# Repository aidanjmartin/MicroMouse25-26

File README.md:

# MicroMouse25-26
This is the repo for SME Robotics Club MicroMouse for 2025-2026 year

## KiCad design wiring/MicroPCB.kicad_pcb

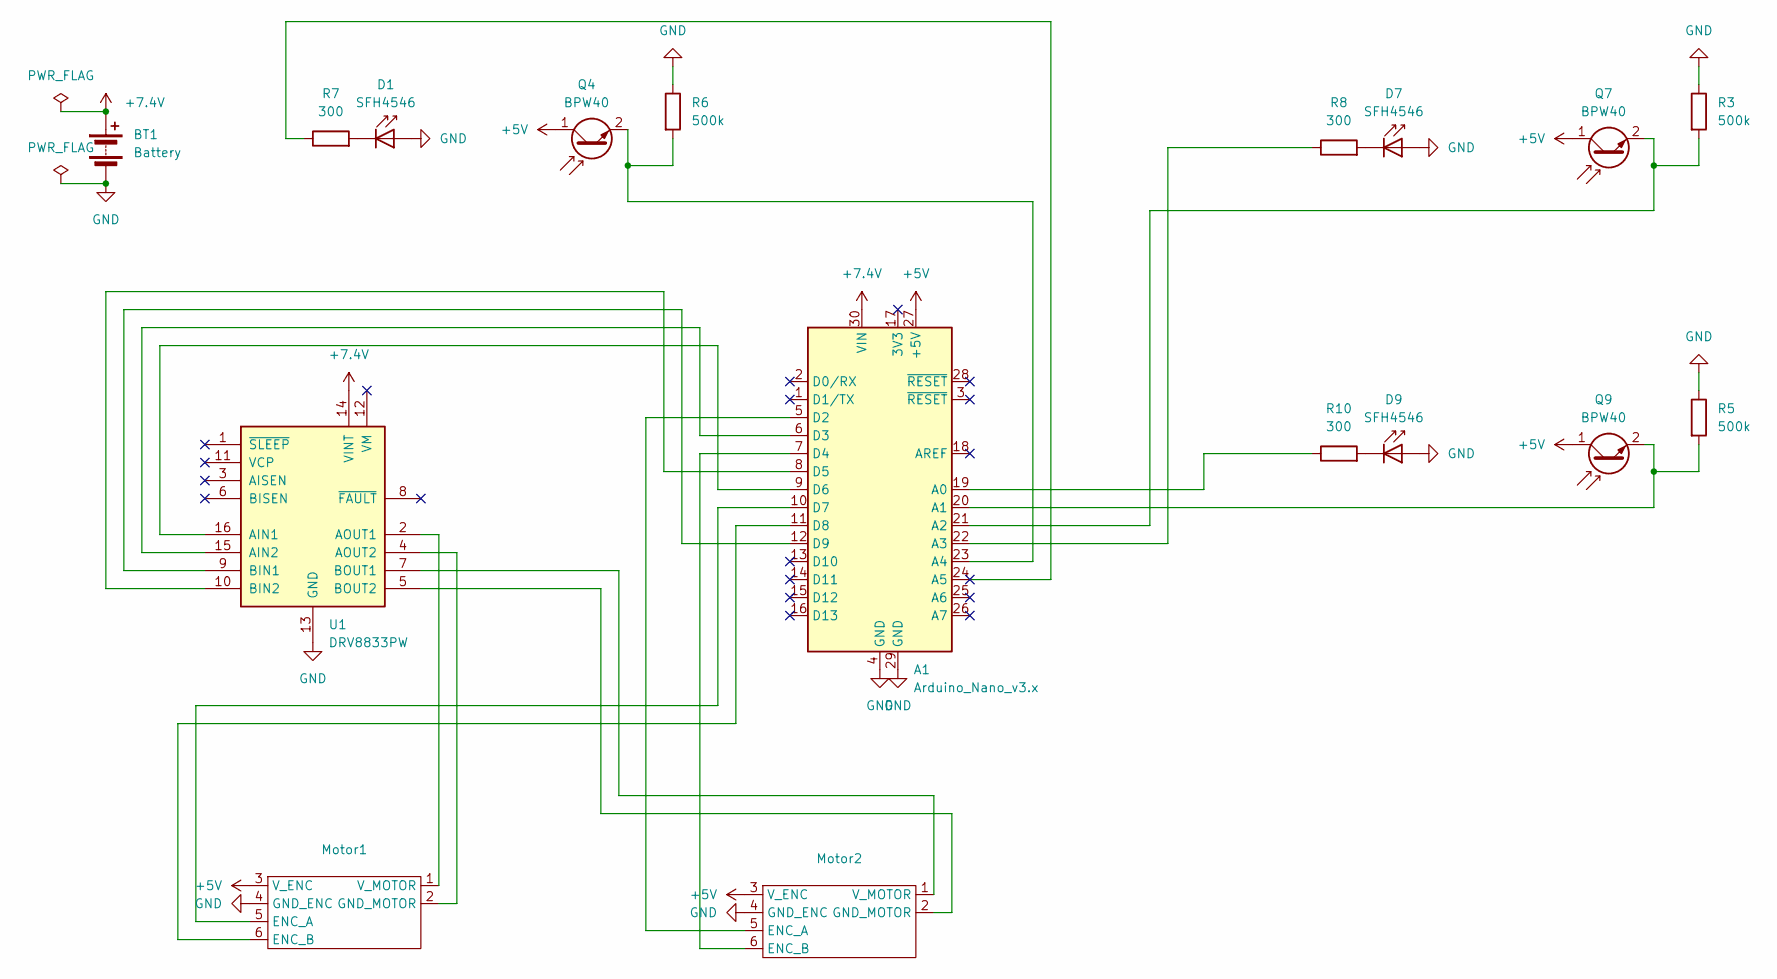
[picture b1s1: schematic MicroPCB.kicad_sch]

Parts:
A1: Arduino_Nano_v3.x; Arduino_Nano
BT1: Battery; PinHeader_1x02_P2.54mm_Horizontal
D1, D7, D9: SFH4546; LED_D5.0mm_IRGrey
Motor1, Motor2: PinHeader_1x06_P2.54mm_Vertical
Q4, Q7, Q9: BPW40; LED_D5.0mm_Clear
R3, R5, R6: 500k; R_Axial_DIN0207_L6.3mm_D2.5mm_P7.62mm_Horizontal
R7, R8, R10: 300; R_Axial_DIN0207_L6.3mm_D2.5mm_P7.62mm_Horizontal
U1: DRV8833PW; TSSOP-16_20.5x13mm_P0.65mm

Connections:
+5V: A1.27 (+5V), Motor1.3 (V_ENC), Motor2.3 (V_ENC), Q4.1 (C), Q7.1 (C), Q9.1 (C)
+7.4V: A1.30 (VIN), BT1.1 (+), U1.14 (VINT)
GND: A1.4 (GND), A1.29 (GND), BT1.2 (-), D1.2 (A), D7.2 (A), D9.2 (A), Motor1.4 (GND_ENC), Motor2.4 (GND_ENC), R3.1, R5.1, R6.1, U1.13 (GND)
unnamed: A1.19 (A0), R10.1
unnamed: A1.20 (A1), Q9.2 (E), R5.2
unnamed: A1.21 (A2), Q7.2 (E), R3.2
unnamed: A1.22 (A3), R8.1
unnamed: A1.23 (A4), Q4.2 (E), R6.2
unnamed: A1.5 (D2), Motor2.5 (ENC_A)
unnamed: A1.6 (D3), U1.15 (AIN2)
unnamed: A1.7 (D4), Motor2.6 (ENC_B)
unnamed: A1.8 (D5), U1.10 (BIN2)
unnamed: A1.9 (D6), U1.16 (AIN1)
unnamed: A1.10 (D7), Motor1.5 (ENC_A)
unnamed: A1.11 (D8), Motor1.6 (ENC_B)
unnamed: A1.12 (D9), U1.9 (BIN1)
unnamed: D1.1 (K), R7.2
unnamed: D7.1 (K), R8.2
unnamed: D9.1 (K), R10.2
unnamed: Motor1.2 (GND_MOTOR), U1.4 (AOUT2)
unnamed: Motor1.1 (V_MOTOR), U1.2 (AOUT1)
unnamed: Motor2.2 (GND_MOTOR), U1.5 (BOUT2)
unnamed: Motor2.1 (V_MOTOR), U1.7 (BOUT1)

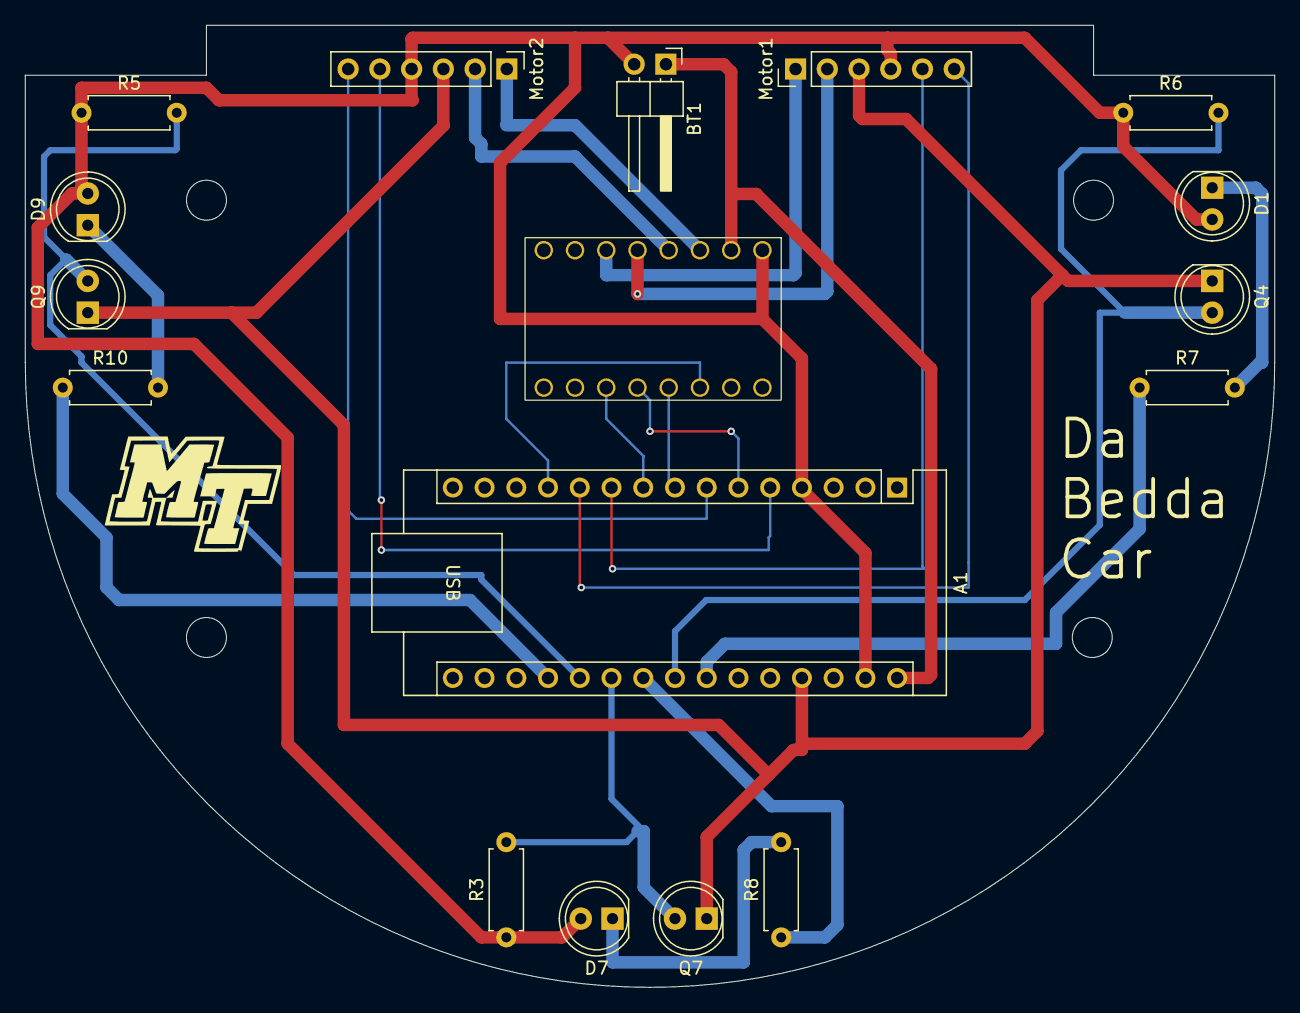
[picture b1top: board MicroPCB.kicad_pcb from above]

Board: 2 copper layers, 100.0 x 77.0 mm, 17 parts (0 on the bottom side), 23 nets.

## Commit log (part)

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2025-09-17 Initial Commit: source code
2026-05-03 PCB Design
2026-05-05 add wiring diagram
2026-05-05 Add hello to readme.md
